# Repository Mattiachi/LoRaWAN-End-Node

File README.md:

# LoRaWAN-End-Node
Project HW and FW of a LoRaWAN end-node with a low power consumption &lt; 1uW

This project is based on a PIC18LF46K22 and the LoRaWAN transceiver SX1276.
The board is powered up by two AAA batteries in series and stays in sleep with a current of around 50 nA. 
After an amount of time set by the resistance Rext, the timer TPL5010 wakes up the PIC18, wich is responsible of measuring the temperature and sending it to a nearby LoRaWAN gateway via ABP (Activation by Personalization).

With this arrangement, transmitting every 15-30 minutes at the lowest SF possible, the estimated life battery can range between 2 to 8 years.

There is a wake button, wich can instantly wake up the board, a ICSP programming port for PICKIT3 or 4 and two rows of 8 pins (distanced 2.54mm) that allow to solder on top of the PCB the [LoRa Olimex module](https://www.olimex.com/Products/IoT/LoRa/LoRa868/open-source-hardware). 

For further information refer to my [thesis document](https://amslaurea.unibo.it/26629)
where the project is explained in more detail.

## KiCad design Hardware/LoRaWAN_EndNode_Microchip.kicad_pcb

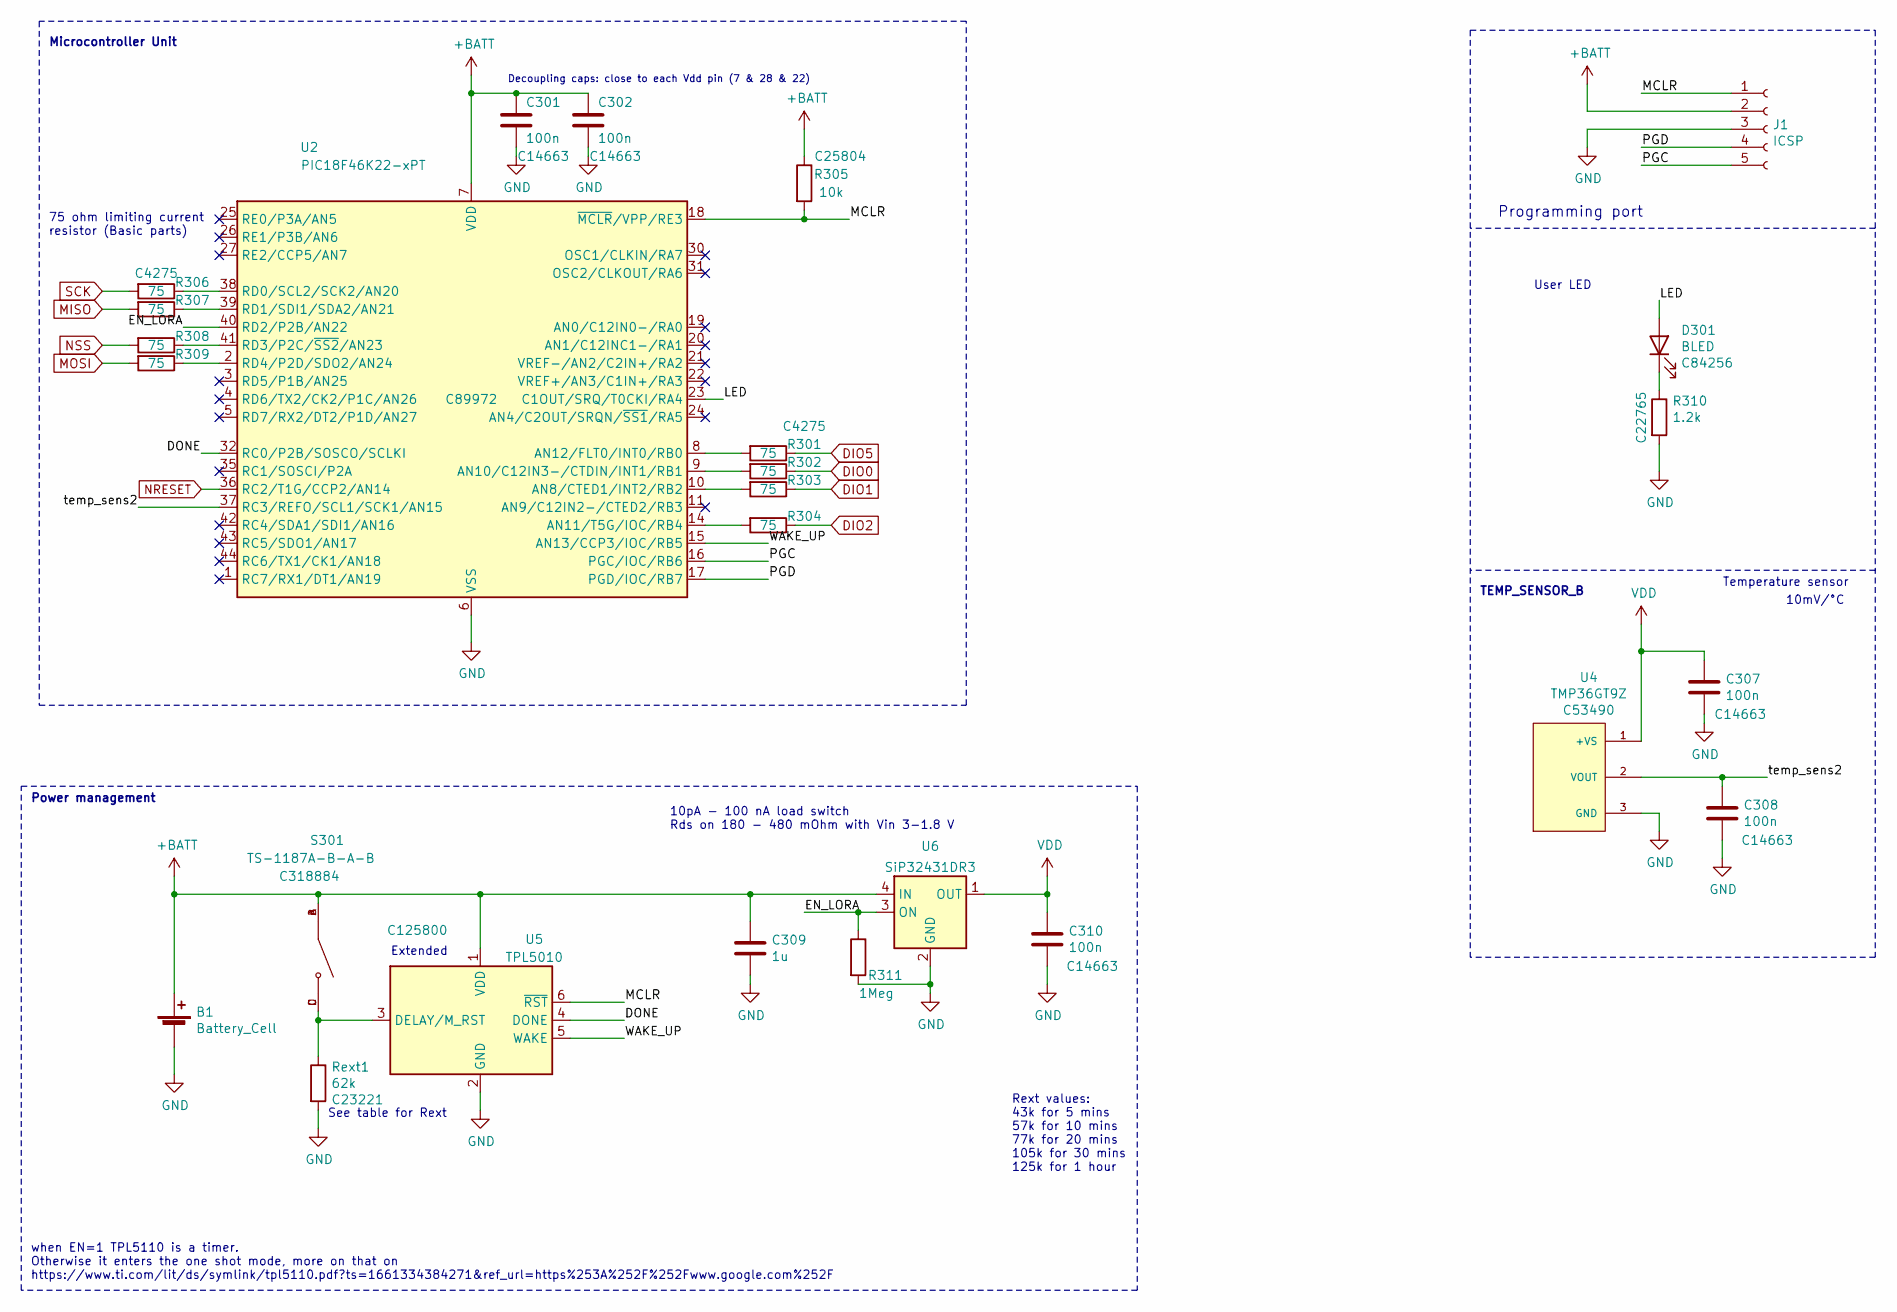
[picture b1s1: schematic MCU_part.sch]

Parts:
B1: Battery_Cell; BatteryHolder_Keystone_2468_2xAAA; MPN 2468
C301, C302, C307, C308, C310: 100n; C_0603_1608Metric; MPN CC0603KRX7R9BB104; LCSC C14663
C309: 1u; C_0603_1608Metric; MPN CC0603KRX7R7BB105
D301: BLED; LED_0805_2012Metric; MPN NCD0805R1; LCSC C84256
J1: ICSP; PinHeader_1x05_P2.54mm_Vertical
R301, R302, R303, R304, R306, R307, R308, R309: 75; R_0603_1608Metric; MPN 0603WAF750JT5E; LCSC C4275
R305: 10k; R_0603_1608Metric; MPN 0603WAF1002T5E; LCSC C25804
R310: 1.2k; R_0603_1608Metric; MPN 0603WAF1201T5E; LCSC C22765
R311: 1Meg; R_0603_1608Metric; MPN 0603WAF1002T5E; LCSC C25804
Rext1: 62k; R_0603_1608Metric; MPN 0603WAF6202T5E; LCSC C23221
S301: TS-1187A-B-A-B; SW_TS-1187A-B-A-B; PARTREV A0; LCSC C318884
U2: PIC18F46K22-xPT; TQFP-44_10x10mm_P0.8mm; MPN PIC18F46K22-I/PT; LCSC C89972
U4: TMP36GT9Z; TO92127P521H733-3; PARTREV H; LCSC C53490
U5: TPL5010; SOT-23-6; MPN TPL5010DDCT; LCSC C125800
U6: SiP32431DR3; SOT-363_SC-70-6; MPN SIP32431DR3-T1GE3; LCSC C141606

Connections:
+BATT: B1.1 (+), C301.1, C302.1, C309.1, J1.2, R305.1, S301.A, S301.B, U2.7 (VDD), U2.28 (VDD), U5.1 (VDD), U6.4 (IN)
/MCU_part/DONE: U2.32 (RC0/P2B/SOSCO/SCLKI), U5.4 (DONE)
/MCU_part/EN_LORA: R311.1, U2.40 (RD2/P2B/AN22), U6.3 (ON)
/MCU_part/LED: D301.2 (A), U2.23 (C1OUT/SRQ/T0CKI/RA4)
/MCU_part/MCLR: J1.1, R305.2, U2.18 (~MCLR~/VPP/RE3), U5.6 (~RST)
/MCU_part/PGC: J1.5, U2.16 (PGC/IOC/RB6)
/MCU_part/PGD: J1.4, U2.17 (PGD/IOC/RB7)
/MCU_part/WAKE_UP: U2.15 (AN13/CCP3/IOC/RB5), U5.5 (WAKE)
/MCU_part/temp_sens2: C308.2, U2.37 (RC3/REFO/SCL1/SCK1/AN15), U4.2 (VOUT)
DIO0: R302.1; also elsewhere on the board
DIO1: R303.1; also elsewhere on the board
DIO2: R304.1; also elsewhere on the board
DIO5: R301.1; also elsewhere on the board
GND: B1.2 (-), C301.2, C302.2, C307.1, C308.1, C309.2, C310.2, J1.3, R310.2, R311.2, Rext1.2, U2.6 (VSS), U2.29 (VSS), U4.3 (GND), U5.2 (GND), U6.2 (GND), U6.5 (GND); also elsewhere on the board
MISO: R307.2; also elsewhere on the board
MOSI: R309.2; also elsewhere on the board
NRESET: U2.36 (RC2/T1G/CCP2/AN14); also elsewhere on the board
NSS: R308.2; also elsewhere on the board
unnamed: D301.1 (K), R310.1
unnamed: R301.2, U2.8 (AN12/FLT0/INT0/RB0)
unnamed: R302.2, U2.9 (AN10/C12IN3-/CTDIN/INT1/RB1)
unnamed: R303.2, U2.10 (AN8/CTED1/INT2/RB2)
unnamed: R304.2, U2.14 (AN11/T5G/IOC/RB4)
unnamed: R306.1, U2.38 (RD0/SCL2/SCK2/AN20)
unnamed: R307.1, U2.39 (RD1/SDI1/SDA2/AN21)
unnamed: R308.1, U2.41 (RD3/P2C/~SS2~/AN23)
unnamed: R309.1, U2.2 (RD4/P2D/SDO2/AN24)
unnamed: Rext1.1, S301.C, S301.D, U5.3 (DELAY/M_RST)
SCK: R306.2; also elsewhere on the board
VDD: C307.2, C310.1, U4.1 (+VS), U6.1 (OUT); also elsewhere on the board

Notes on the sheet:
Decoupling caps: close to each Vdd pin (7 & 28 & 22)
Programming port
75 ohm limiting current resistor (Basic parts)
Temperature sensor
10mV/°C
TEMP_SENSOR_B
when EN=1 TPL5110 is a timer. Otherwise it enters the one shot mode, more on that on https://www.ti.com/lit/ds/symlink/tpl5110.pdf?ts=1661334384271&ref_url=https%253A%252F%252Fwww.google.com%252F
Power management
Microcontroller Unit
Extended
10pA - 100 nA load switch Rds on 180 - 480 mOhm with Vin 3-1.8 V
Rext values: 43k for 5 mins 57k for 10 mins 77k for 20 mins 105k for 30 mins 125k for 1 hour
See table for Rext
User LED

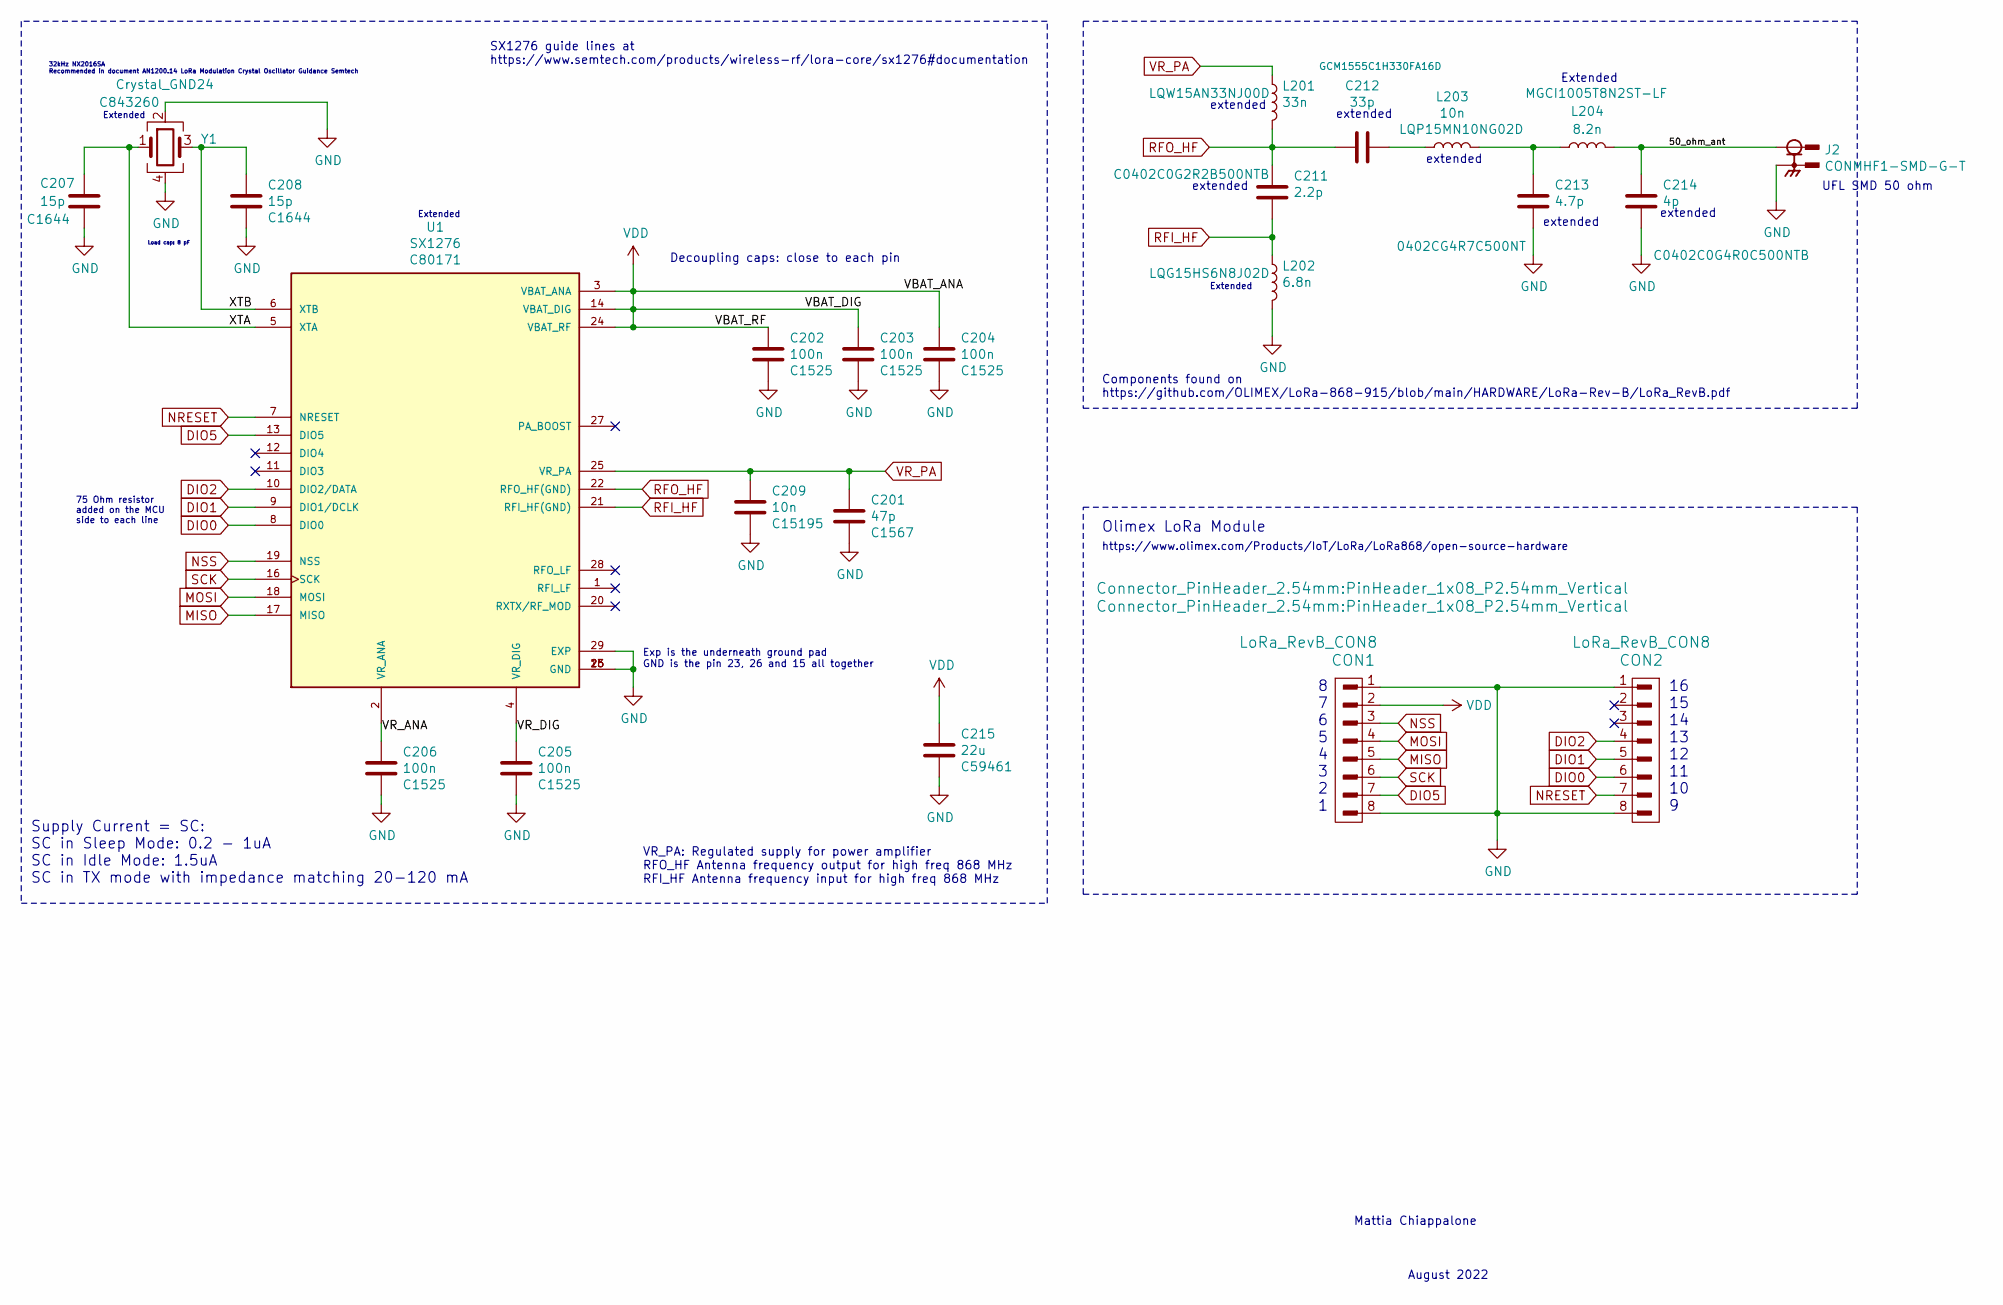
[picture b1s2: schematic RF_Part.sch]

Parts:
C201: 47p; C_0402_1005Metric; MPN 0402CG470J500NT; LCSC C1567
C202, C203, C204, C205, C206: 100n; C_0402_1005Metric; MPN CL05B104KO5NNNC; LCSC C1525
C207, C208: 15p; C_0603_1608Metric; MPN CL10C150JB8NNNC; LCSC C1644
C209: 10n; C_0402_1005Metric; MPN CL05B103KB5NNNC; LCSC C15195
C211: 2.2p; C_0402_1005Metric; MPN C0402C0G2R2B500NTB; LCSC C140673
C212: 33p; C_0402_1005Metric; MPN GCM1555C1H330FA16D; LCSC C437439
C213: 4.7p; C_0402_1005Metric; MPN 0402CG4R7C500NT; LCSC C1569
C214: 4p; C_0402_1005Metric; MPN C0402C0G4R0C500NTB; LCSC C140662
C215: 22u; C_0603_1608Metric; MPN CL10A226MQ8NRNC; LCSC C59461
CON1, CON2: LoRa_RevB_CON8; PinHeader_1x08_P2.54mm_Vertical
J2: CONMHF1-SMD-G-T; LINX_CONMHF1-SMD-G-T; PARTREV A
L201: 33n; L_0402_1005Metric; MPN LQW15AN33NJ00D; LCSC C335624
L202: 6.8n; L_0402_1005Metric; MPN LQG15HS6N8J02D; LCSC C77110
L203: 10n; L_0402_1005Metric; MPN LQP15MN10NG02D; LCSC C162639
L204: 8.2n; L_0402_1005Metric; MPN MGCI1005T8N2ST-LF; LCSC C281010
U1: SX1276; QFN65P600X600X100-29N; PARTREV 6; LCSC C80171
Y1: Crystal_GND24; Crystal_SMD_2016-4Pin_2.0x1.6mm; MPN NX2016SA-32MHZ-STD-CZS-5; LCSC C843260

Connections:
/RF_Part/50_ohm_ant: C214.2, J2.1, L204.2
/RF_Part/VR_ANA: C206.1, U1.2 (VR_ANA)
/RF_Part/VR_DIG: C205.1, U1.4 (VR_DIG)
/RF_Part/XTA: C207.1, U1.5 (XTA), Y1.1
/RF_Part/XTB: C208.1, U1.6 (XTB), Y1.3
DIO0: CON2.6, U1.8 (DIO0); also elsewhere on the board
DIO1: CON2.5, U1.9 (DIO1/DCLK); also elsewhere on the board
DIO2: CON2.4, U1.10 (DIO2/DATA); also elsewhere on the board
DIO5: CON1.7, U1.13 (DIO5); also elsewhere on the board
GND: C201.2, C202.2, C203.2, C204.2, C205.2, C206.2, C207.2, C208.2, C209.2, C213.1, C214.1, C215.2, CON1.1, CON1.8, CON2.1, CON2.8, J2.S1, J2.S2, J2.S3, L202.2, U1.15 (GND), U1.23 (GND), U1.26 (GND), U1.29 (EXP), Y1.2, Y1.4; also elsewhere on the board
MISO: CON1.5, U1.17 (MISO); also elsewhere on the board
MOSI: CON1.4, U1.18 (MOSI); also elsewhere on the board
NRESET: CON2.7, U1.7 (NRESET); also elsewhere on the board
NSS: CON1.3, U1.19 (NSS); also elsewhere on the board
unnamed: C212.1, L203.1
unnamed: C213.2, L203.2, L204.1
RFI_HF: C211.2, L202.1, U1.21 (RFI_HF(GND))
RFO_HF: C211.1, C212.2, L201.2, U1.22 (RFO_HF(GND))
SCK: CON1.6, U1.16 (SCK); also elsewhere on the board
VDD: C202.1, C203.1, C204.1, C215.1, CON1.2, U1.3 (VBAT_ANA), U1.14 (VBAT_DIG), U1.24 (VBAT_RF); also elsewhere on the board
VR_PA: C201.1, C209.1, L201.1, U1.25 (VR_PA)

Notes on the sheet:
Exp is the underneath ground pad GND is the pin 23, 26 and 15 all together
32kHz NX2016SA Recommended in document AN1200.14 LoRa Modulation Crystal Oscillator Guidance Semtech
Load cap: 8 pF
SX1276 guide lines at https://www.semtech.com/products/wireless-rf/lora-core/sx1276#documentation
Supply Current = SC: SC in Sleep Mode: 0.2 - 1uA SC in Idle Mode: 1.5uA SC in TX mode with impedance matching 20-120 mA
Decoupling caps: close to each pin
VR_PA: Regulated supply for power amplifier RFO_HF Antenna frequency output for high freq 868 MHz RFI_HF Antenna frequency input for high freq 868 MHz
August 2022
Mattia Chiappalone
Extended
Extended
75 Ohm resistor added on the MCU side to each line
extended
extended
Components found on https://github.com/OLIMEX/LoRa-868-915/blob/main/HARDWARE/LoRa-Rev-B/LoRa_RevB.pdf
8 7 6 5 4 3 2 1
16 15 14 13 12 11 10 9
Olimex LoRa Module
https://www.olimex.com/Products/IoT/LoRa/LoRa868/open-source-hardware
UFL SMD 50 ohm

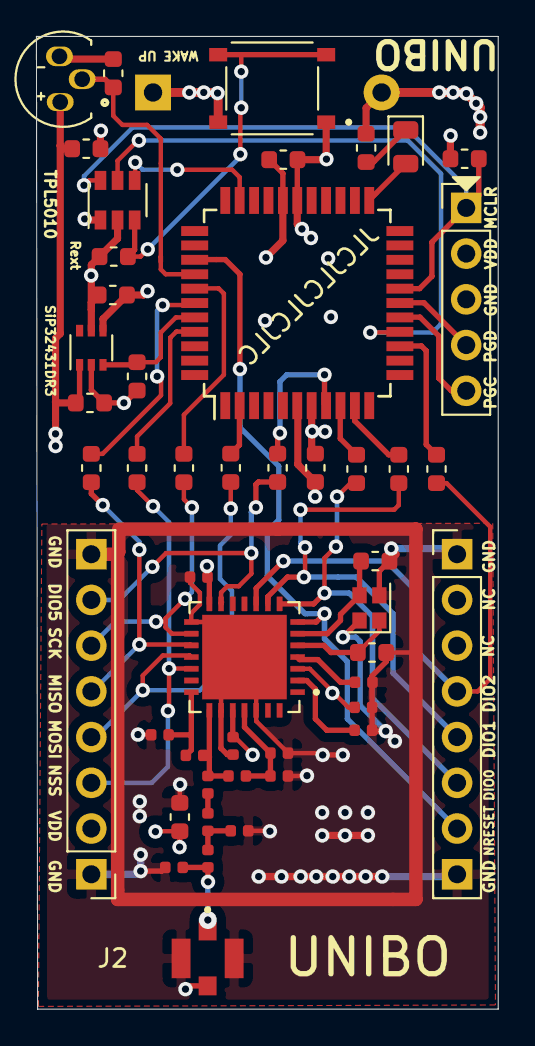
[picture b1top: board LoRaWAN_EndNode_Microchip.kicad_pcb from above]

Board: 4 copper layers, 25.7 x 54.0 mm, 49 parts (1 on the bottom side), 40 nets.

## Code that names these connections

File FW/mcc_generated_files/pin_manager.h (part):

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// get/set LED aliases
#define LED_TRIS               TRISAbits.TRISA4
#define LED_LAT                LATAbits.LATA4
#define LED_PORT               PORTAbits.RA4
#define LED_SetHigh()            do { LATAbits.LATA4 = 1; } while(0)
#define LED_SetLow()             do { LATAbits.LATA4 = 0; } while(0)
#define LED_Toggle()             do { LATAbits.LATA4 = ~LATAbits.LATA4; } while(0)
#define LED_GetValue()           PORTAbits.RA4
#define LED_SetDigitalInput()    do { TRISAbits.TRISA4 = 1; } while(0)
#define LED_SetDigitalOutput()   do { TRISAbits.TRISA4 = 0; } while(0)

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#define RB0_SetHigh()    do { LATBbits.LATB0 = 1; } while(0)
#define RB0_SetLow()   do { LATBbits.LATB0 = 0; } while(0)
#define RB0_Toggle()   do { LATBbits.LATB0 = ~LATBbits.LATB0; } while(0)
#define RB0_GetValue()         PORTBbits.RB0
#define RB0_SetDigitalInput()   do { TRISBbits.TRISB0 = 1; } while(0)
#define RB0_SetDigitalOutput()  do { TRISBbits.TRISB0 = 0; } while(0)
#define RB0_SetPullup()     do { WPUBbits.WPUB0 = 1; } while(0)
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#define RB1_SetHigh()    do { LATBbits.LATB1 = 1; } while(0)
#define RB1_SetLow()   do { LATBbits.LATB1 = 0; } while(0)
#define RB1_Toggle()   do { LATBbits.LATB1 = ~LATBbits.LATB1; } while(0)
#define RB1_GetValue()         PORTBbits.RB1
#define RB1_SetDigitalInput()   do { TRISBbits.TRISB1 = 1; } while(0)
#define RB1_SetDigitalOutput()  do { TRISBbits.TRISB1 = 0; } while(0)
#define RB1_SetPullup()     do { WPUBbits.WPUB1 = 1; } while(0)
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#define RB2_SetHigh()    do { LATBbits.LATB2 = 1; } while(0)
#define RB2_SetLow()   do { LATBbits.LATB2 = 0; } while(0)
#define RB2_Toggle()   do { LATBbits.LATB2 = ~LATBbits.LATB2; } while(0)
#define RB2_GetValue()         PORTBbits.RB2
#define RB2_SetDigitalInput()   do { TRISBbits.TRISB2 = 1; } while(0)
#define RB2_SetDigitalOutput()  do { TRISBbits.TRISB2 = 0; } while(0)
#define RB2_SetPullup()     do { WPUBbits.WPUB2 = 1; } while(0)
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#define RB4_SetHigh()    do { LATBbits.LATB4 = 1; } while(0)
#define RB4_SetLow()   do { LATBbits.LATB4 = 0; } while(0)
#define RB4_Toggle()   do { LATBbits.LATB4 = ~LATBbits.LATB4; } while(0)
#define RB4_GetValue()         PORTBbits.RB4
#define RB4_SetDigitalInput()   do { TRISBbits.TRISB4 = 1; } while(0)
#define RB4_SetDigitalOutput()  do { TRISBbits.TRISB4 = 0; } while(0)
#define RB4_SetPullup()     do { WPUBbits.WPUB4 = 1; } while(0)
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// get/set WAKE_UP aliases
#define WAKE_UP_TRIS               TRISBbits.TRISB5
#define WAKE_UP_LAT                LATBbits.LATB5
#define WAKE_UP_PORT               PORTBbits.RB5
#define WAKE_UP_WPU                WPUBbits.WPUB5
#define WAKE_UP_ANS                ANSELBbits.ANSB5
#define WAKE_UP_SetHigh()            do { LATBbits.LATB5 = 1; } while(0)
#define WAKE_UP_SetLow()             do { LATBbits.LATB5 = 0; } while(0)
#define WAKE_UP_Toggle()             do { LATBbits.LATB5 = ~LATBbits.LATB5; } while(0)
#define WAKE_UP_GetValue()           PORTBbits.RB5
#define WAKE_UP_SetDigitalInput()    do { TRISBbits.TRISB5 = 1; } while(0)
#define WAKE_UP_SetDigitalOutput()   do { TRISBbits.TRISB5 = 0; } while(0)
#define WAKE_UP_SetPullup()      do { WPUBbits.WPUB5 = 1; } while(0)
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// get/set DONE aliases
#define DONE_TRIS               TRISCbits.TRISC0
#define DONE_LAT                LATCbits.LATC0
#define DONE_PORT               PORTCbits.RC0
#define DONE_SetHigh()            do { LATCbits.LATC0 = 1; } while(0)
#define DONE_SetLow()             do { LATCbits.LATC0 = 0; } while(0)
#define DONE_Toggle()             do { LATCbits.LATC0 = ~LATCbits.LATC0; } while(0)
#define DONE_GetValue()           PORTCbits.RC0
#define DONE_SetDigitalInput()    do { TRISCbits.TRISC0 = 1; } while(0)
#define DONE_SetDigitalOutput()   do { TRISCbits.TRISC0 = 0; } while(0)

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#define RC2_SetHigh()    do { LATCbits.LATC2 = 1; } while(0)
#define RC2_SetLow()   do { LATCbits.LATC2 = 0; } while(0)
#define RC2_Toggle()   do { LATCbits.LATC2 = ~LATCbits.LATC2; } while(0)
#define RC2_GetValue()         PORTCbits.RC2
#define RC2_SetDigitalInput()   do { TRISCbits.TRISC2 = 1; } while(0)
#define RC2_SetDigitalOutput()  do { TRISCbits.TRISC2 = 0; } while(0)
#define RC2_SetAnalogMode() do { ANSELCbits.ANSC2 = 1; } while(0)
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// get/set TEMP aliases
#define TEMP_TRIS               TRISCbits.TRISC3
#define TEMP_LAT                LATCbits.LATC3
#define TEMP_PORT               PORTCbits.RC3
#define TEMP_ANS                ANSELCbits.ANSC3
#define TEMP_SetHigh()            do { LATCbits.LATC3 = 1; } while(0)
#define TEMP_SetLow()             do { LATCbits.LATC3 = 0; } while(0)
#define TEMP_Toggle()             do { LATCbits.LATC3 = ~LATCbits.LATC3; } while(0)
#define TEMP_GetValue()           PORTCbits.RC3
#define TEMP_SetDigitalInput()    do { TRISCbits.TRISC3 = 1; } while(0)
#define TEMP_SetDigitalOutput()   do { TRISCbits.TRISC3 = 0; } while(0)
#define TEMP_SetAnalogMode()  do { ANSELCbits.ANSC3 = 1; } while(0)
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#define RD0_SetHigh()    do { LATDbits.LATD0 = 1; } while(0)
#define RD0_SetLow()   do { LATDbits.LATD0 = 0; } while(0)
#define RD0_Toggle()   do { LATDbits.LATD0 = ~LATDbits.LATD0; } while(0)
#define RD0_GetValue()         PORTDbits.RD0
#define RD0_SetDigitalInput()   do { TRISDbits.TRISD0 = 1; } while(0)
#define RD0_SetDigitalOutput()  do { TRISDbits.TRISD0 = 0; } while(0)
#define RD0_SetAnalogMode() do { ANSELDbits.ANSD0 = 1; } while(0)
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#define RD1_SetHigh()    do { LATDbits.LATD1 = 1; } while(0)
#define RD1_SetLow()   do { LATDbits.LATD1 = 0; } while(0)
#define RD1_Toggle()   do { LATDbits.LATD1 = ~LATDbits.LATD1; } while(0)
#define RD1_GetValue()         PORTDbits.RD1
#define RD1_SetDigitalInput()   do { TRISDbits.TRISD1 = 1; } while(0)
#define RD1_SetDigitalOutput()  do { TRISDbits.TRISD1 = 0; } while(0)
#define RD1_SetAnalogMode() do { ANSELDbits.ANSD1 = 1; } while(0)
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// get/set EN_LORA aliases
#define EN_LORA_TRIS               TRISDbits.TRISD2
#define EN_LORA_LAT                LATDbits.LATD2
#define EN_LORA_PORT               PORTDbits.RD2
#define EN_LORA_ANS                ANSELDbits.ANSD2
#define EN_LORA_SetHigh()            do { LATDbits.LATD2 = 1; } while(0)
#define EN_LORA_SetLow()             do { LATDbits.LATD2 = 0; } while(0)
#define EN_LORA_Toggle()             do { LATDbits.LATD2 = ~LATDbits.LATD2; } while(0)
#define EN_LORA_GetValue()           PORTDbits.RD2
#define EN_LORA_SetDigitalInput()    do { TRISDbits.TRISD2 = 1; } while(0)
#define EN_LORA_SetDigitalOutput()   do { TRISDbits.TRISD2 = 0; } while(0)
#define EN_LORA_SetAnalogMode()  do { ANSELDbits.ANSD2 = 1; } while(0)
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#define RD3_SetHigh()    do { LATDbits.LATD3 = 1; } while(0)
#define RD3_SetLow()   do { LATDbits.LATD3 = 0; } while(0)
#define RD3_Toggle()   do { LATDbits.LATD3 = ~LATDbits.LATD3; } while(0)
#define RD3_GetValue()         PORTDbits.RD3
#define RD3_SetDigitalInput()   do { TRISDbits.TRISD3 = 1; } while(0)
#define RD3_SetDigitalOutput()  do { TRISDbits.TRISD3 = 0; } while(0)
#define RD3_SetAnalogMode() do { ANSELDbits.ANSD3 = 1; } while(0)
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#define RD4_SetHigh()    do { LATDbits.LATD4 = 1; } while(0)
#define RD4_SetLow()   do { LATDbits.LATD4 = 0; } while(0)
#define RD4_Toggle()   do { LATDbits.LATD4 = ~LATDbits.LATD4; } while(0)
#define RD4_GetValue()         PORTDbits.RD4
#define RD4_SetDigitalInput()   do { TRISDbits.TRISD4 = 1; } while(0)
#define RD4_SetDigitalOutput()  do { TRISDbits.TRISD4 = 0; } while(0)
#define RD4_SetAnalogMode() do { ANSELDbits.ANSD4 = 1; } while(0)
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
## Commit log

2022-09-20 Create FW

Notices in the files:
FW/mcc_generated_files/pin_manager.h:
Copyright (c) 2013 - 2015 released Microchip Technology Inc.  All rights reserved.
